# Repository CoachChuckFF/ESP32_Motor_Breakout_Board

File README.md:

# Will Oddjob 1 - ESP Breakout Board

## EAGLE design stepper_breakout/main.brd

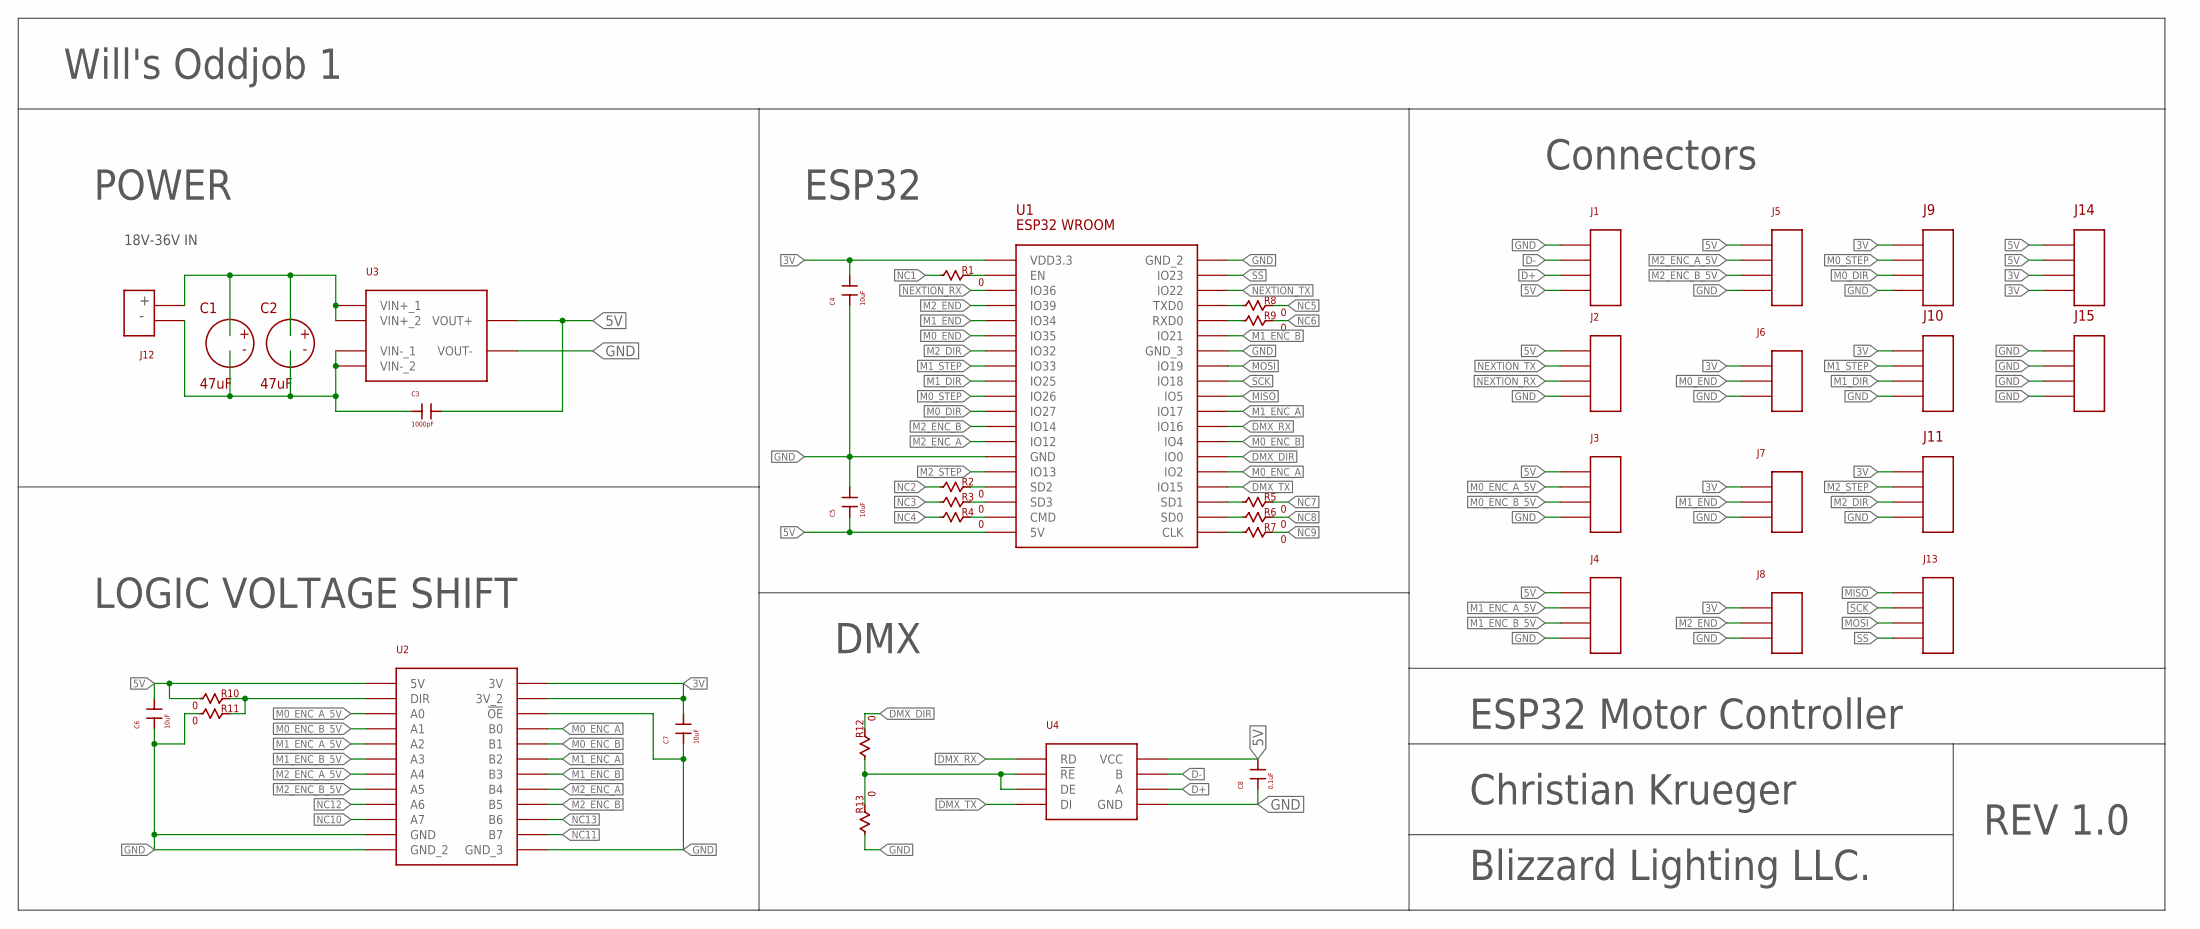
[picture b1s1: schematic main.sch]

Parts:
C1, C2: 47uF; TH_CAP_PKG
C3: 1000pF; 1808_PKG
C4, C5, C6, C7: 10uF; 0805_PKG
C8: 0.1uF; 0805_PKG
J1, J2, J3, J4, J5: XH_4POS_DEV; XH_4POS_PKG
J6, J7, J8: XH_3POS_DEV; XH_3POS_PKG
J9, J10, J11, J14, J15: 4_PIN_SCREW_3.5MM_DEV; 4_PIN_SCREW_3.5MM_PKG
J12: 2_PIN_SCREW_3.5MM_DEV; 2_PIN_SCREW_3.5MM_PKG
J13: 4_PIN_2.54MM_PKG
R1, R2, R3, R4, R5, R6, R7, R8, R9, R10, R11, R12, R13: 0; 0805_PKG
U1: ESP32_WROOM_BREAKOUT_DEV; ESP_WROOM_BREAKOUT_PKG
U2: 8_CHANNEL_LEVEL_SHIFTER; 8_LEVEL_SHIFTER_PKG
U3: 5V_SWITCHING_POWER_DEV; 5V_SWITCHING_POWER_PKG
U4: MAX_485_DEV; MAX_485_PKG

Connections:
3V: C4.P$2, C7.P$2, J6.P$1 (1), J7.P$1 (1), J8.P$1 (1), J9.1, J10.1, J11.1, J14.3, J14.4, U1.VDD3.3, U2.3V, U2.3V_2
5V: C3.P$2, C5.P$1, C6.P$2, C8.P$2, J1.P$4, J2.P$1, J3.P$1, J4.P$1, J5.P$1, J14.1, J14.2, R10.P$1, U1.5V, U2.5V, U3.VOUT+, U4.P$8 (VCC)
D+: J1.P$3, U4.P$6 (A)
D-: J1.P$2, U4.P$7 (B)
DMX_DIR: R12.P$2, U1.IO0
DMX_RX: U1.IO16, U4.P$1 (RD)
DMX_TX: U1.IO15, U4.P$4 (DI)
GND: C4.P$1, C5.P$2, C6.P$1, C7.P$1, C8.P$1, J1.P$1, J2.P$4, J3.P$4, J4.P$4, J5.P$4, J6.P$3 (3), J7.P$3 (3), J8.P$3 (3), J9.4, J10.4, J11.4, J15.1, J15.2, J15.3, J15.4, R11.P$1, R13.P$1, U1.GND, U1.GND_2, U1.GND_3, U2.!OE, U2.GND, U2.GND_2, U2.GND_3, U3.VOUT-, U4.P$5 (GND)
M0_DIR: J9.3, U1.IO27
M0_ENC_A: U1.IO2, U2.B0
M0_ENC_A_5V: J3.P$2, U2.A0
M0_ENC_B: U1.IO4, U2.B1
M0_ENC_B_5V: J3.P$3, U2.A1
M0_END: J6.P$2 (2), U1.IO35
M0_STEP: J9.2, U1.IO26
M1_DIR: J10.3, U1.IO25
M1_ENC_A: U1.IO17, U2.B2
M1_ENC_A_5V: J4.P$2, U2.A2
M1_ENC_B: U1.IO21, U2.B3
M1_ENC_B_5V: J4.P$3, U2.A3
M1_END: J7.P$2 (2), U1.IO34
M1_STEP: J10.2, U1.IO33
M2_DIR: J11.3, U1.IO32
M2_ENC_A: U1.IO12, U2.B4
M2_ENC_A_5V: J5.P$2, U2.A4
M2_ENC_B: U1.IO14, U2.B5
M2_ENC_B_5V: J5.P$3, U2.A5
M2_END: J8.P$2 (2), U1.IO39
M2_STEP: J11.2, U1.IO13
MISO: J13.1, U1.IO5
MOSI: J13.3, U1.IO19
unnamed: C1.P$1, C2.P$1, J12.P$2 (2), U3.VIN+_1, U3.VIN+_2
unnamed: C1.P$2, C2.P$2, C3.P$1, J12.P$1 (1), U3.VIN-_1, U3.VIN-_2
unnamed: R1.P$2, U1.EN
unnamed: R12.P$1, R13.P$2, U4.P$2 (!RE), U4.P$3 (DE)
unnamed: R2.P$2, U1.SD2
unnamed: R3.P$2, U1.SD3
unnamed: R4.P$2, U1.CMD
unnamed: R10.P$2, R11.P$2, U2.DIR
unnamed: R7.P$1, U1.CLK
unnamed: R6.P$1, U1.SD0
unnamed: R5.P$1, U1.SD1
unnamed: R8.P$1, U1.TXD0
unnamed: R9.P$1, U1.RXD0
NC1: R1.P$1
NC2: R2.P$1
NC3: R3.P$1
NC4: R4.P$1
NC5: R8.P$2
NC6: R9.P$2
NC7: R5.P$2
NC8: R6.P$2
NC9: R7.P$2
NC10: U2.A7
NC11: U2.B7
NC12: U2.A6
NC13: U2.B6
NEXTION_RX: J2.P$3, U1.IO36
NEXTION_TX: J2.P$2, U1.IO22
SCK: J13.2, U1.IO18
SS: J13.4, U1.IO23

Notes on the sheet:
18V-36V IN
POWER
ESP32
LOGIC VOLTAGE SHIFT
DMX
Connectors
Will's Oddjob 1
REV 1.0
Christian Krueger
Blizzard Lighting LLC.
ESP32 Motor Controller

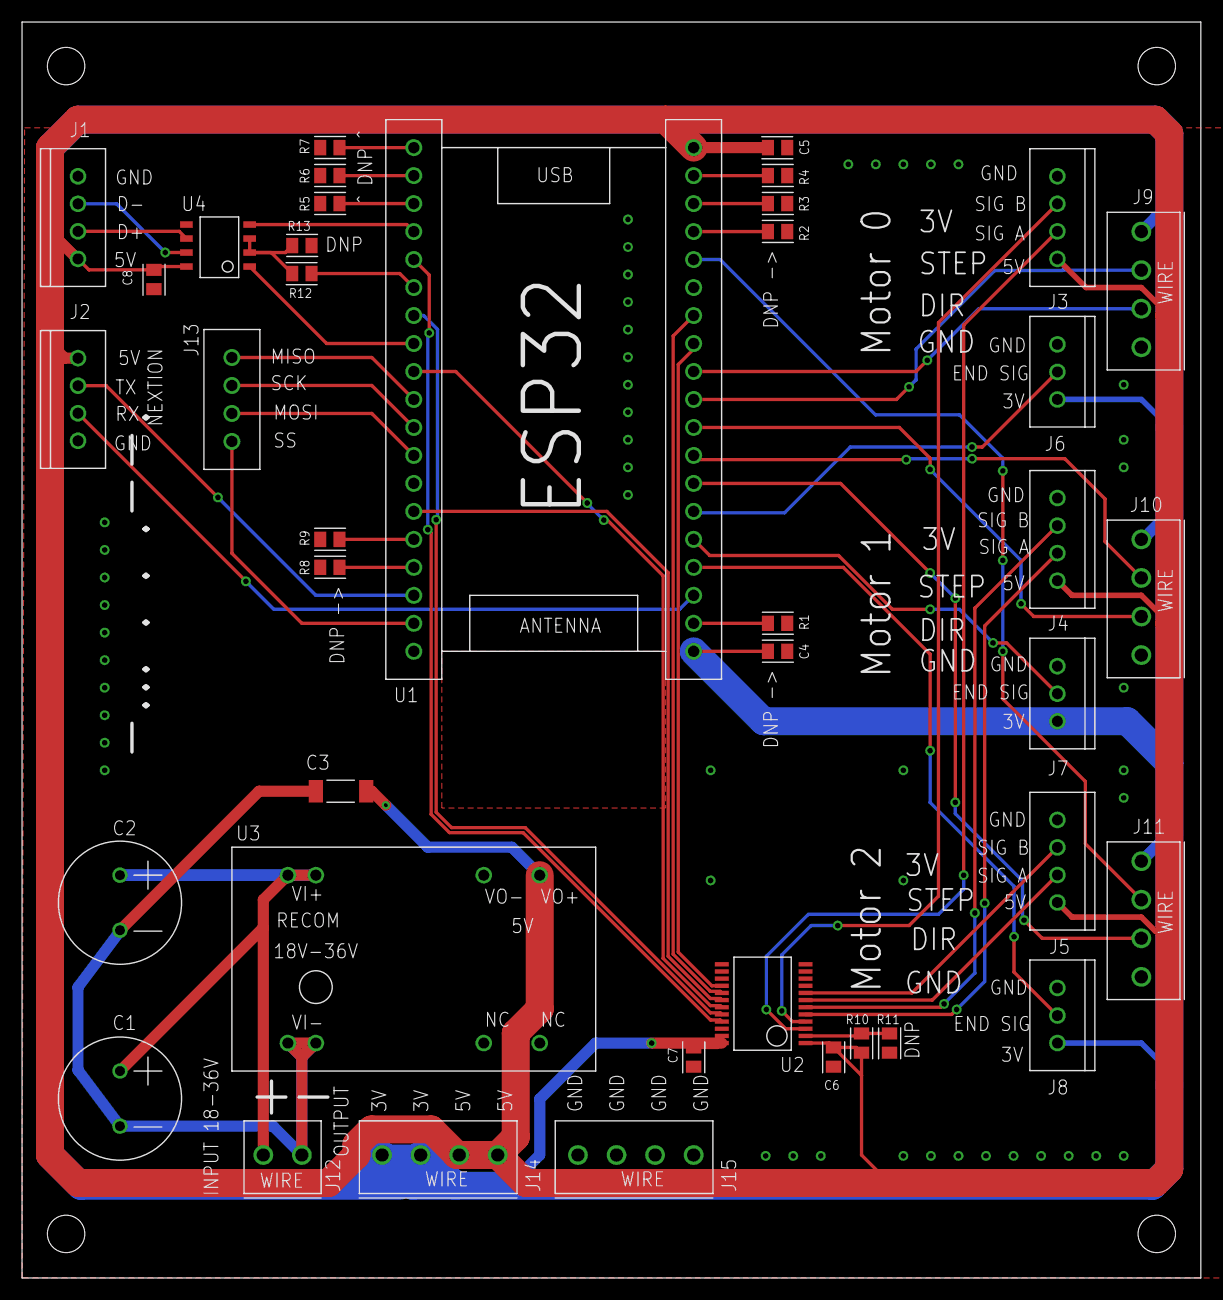
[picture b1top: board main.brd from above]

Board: 2 copper layers, 107.0 x 114.0 mm, 40 parts (0 on the bottom side), 48 nets.

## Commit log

2017-11-01 first
2017-11-02 sch almost done
2017-11-02 rev1 done
2017-11-02 ordered
